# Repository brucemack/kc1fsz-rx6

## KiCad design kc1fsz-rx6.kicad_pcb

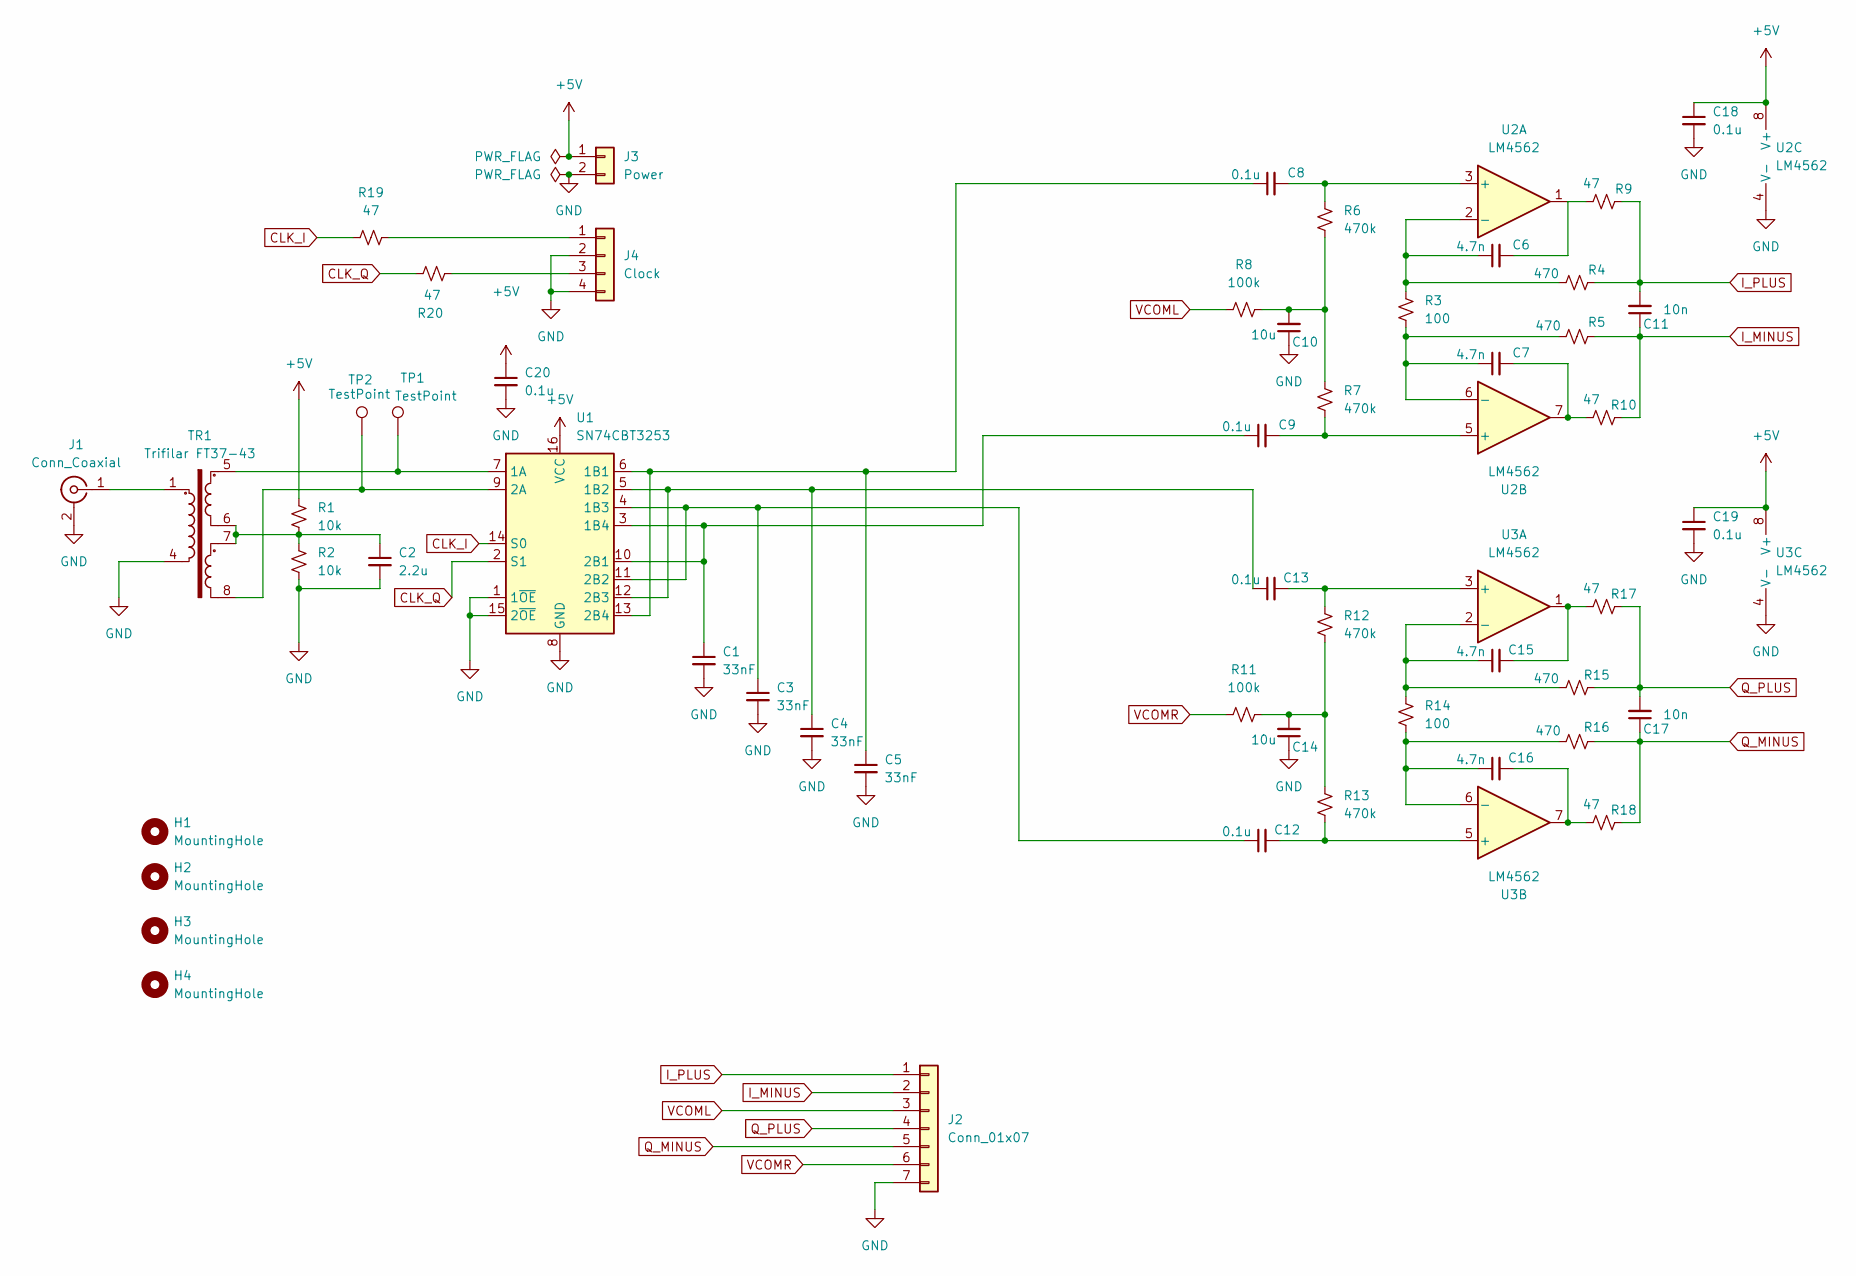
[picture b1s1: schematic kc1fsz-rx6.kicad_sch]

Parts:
C1, C3, C4, C5: 33nF; C_0805_2012Metric_Pad1.18x1.45mm_HandSolder
C2: 2.2u; C_0805_2012Metric_Pad1.18x1.45mm_HandSolder
C6, C7, C15, C16: 4.7n; C_0805_2012Metric_Pad1.18x1.45mm_HandSolder
C8, C9, C12, C13, C18, C19, C20: 0.1u; C_0805_2012Metric_Pad1.18x1.45mm_HandSolder
C10, C14: 10u; C_0805_2012Metric_Pad1.18x1.45mm_HandSolder
C11, C17: 10n; C_0805_2012Metric_Pad1.18x1.45mm_HandSolder
H1, H2, H3, H4: MountingHole; MountingHole_3.5mm
J1: Conn_Coaxial; SMA_Amphenol_901-144_Vertical
J2: Conn_01x07; PinHeader_1x07_P2.54mm_Vertical
J3: Power; PinHeader_1x02_P2.54mm_Vertical
J4: Clock; PinHeader_1x04_P2.54mm_Vertical
R1, R2: 10k; R_0805_2012Metric_Pad1.20x1.40mm_HandSolder
R3, R14: 100; R_0805_2012Metric_Pad1.20x1.40mm_HandSolder
R4, R5, R15, R16: 470; R_0805_2012Metric_Pad1.20x1.40mm_HandSolder
R6, R7, R12, R13: 470k; R_0805_2012Metric_Pad1.20x1.40mm_HandSolder
R8, R11: 100k; R_0805_2012Metric_Pad1.20x1.40mm_HandSolder
R9, R10, R17, R18, R19, R20: 47; R_0805_2012Metric_Pad1.20x1.40mm_HandSolder
TP1, TP2: TestPoint; TestPoint_Pad_1.5x1.5mm
TR1: Trifilar FT37-43; FT37-43 Trifilar
U1: SN74CBT3253; SOIC-16_3.9x9.9mm_P1.27mm
U2, U3: LM4562; SOIC-8_3.9x4.9mm_P1.27mm

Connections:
+5V: C18.1, C19.1, C20.1, J3.1, R1.1, U1.16 (VCC), U2.8 (V+), U3.8 (V+)
CLK_I: R19.1, U1.14 (S0)
CLK_Q: R20.1, U1.2 (S1)
GND: C1.2, C2.2, C3.2, C4.2, C5.2, C10.1, C14.1, C18.2, C19.2, C20.2, J1.2 (Ext), J2.7, J3.2, J4.2, J4.4, R2.2, TR1.4, U1.1 (1~OE), U1.8 (GND), U1.15 (2~OE), U2.4 (V-), U3.4 (V-)
I_MINUS: C11.1, J2.2, R5.2, R10.2
I_PLUS: C11.2, J2.1, R4.2, R9.2
unnamed: C2.1, R1.2, R2.1, TR1.6, TR1.7
unnamed: C6.2, R9.1, U2.1
unnamed: C7.2, R10.1, U2.7
unnamed: C10.2, R6.2, R7.1, R8.2
unnamed: C14.2, R11.2, R12.2, R13.1
unnamed: C15.2, R17.1, U3.1
unnamed: C16.2, R18.1, U3.7
unnamed: J1.1 (In), TR1.1
unnamed: J4.1, R19.2
unnamed: J4.3, R20.2
unnamed: TP1.1, TR1.5, U1.7 (1A)
unnamed: C5.1, C8.1, U1.6 (1B1), U1.13 (2B4)
unnamed: C4.1, C13.1, U1.5 (1B2), U1.12 (2B3)
unnamed: C3.1, C12.1, U1.4 (1B3), U1.11 (2B2)
unnamed: C1.1, C9.1, U1.3 (1B4), U1.10 (2B1)
unnamed: TP2.1, TR1.8, U1.9 (2A)
unnamed: C8.2, R6.1, U2.3 (+)
unnamed: C6.1, R3.1, R4.1, U2.2 (-)
unnamed: C9.2, R7.2, U2.5 (+)
unnamed: C7.1, R3.2, R5.1, U2.6 (-)
unnamed: C13.2, R12.1, U3.3 (+)
unnamed: C15.1, R14.1, R15.1, U3.2 (-)
unnamed: C12.2, R13.2, U3.5 (+)
unnamed: C16.1, R14.2, R16.1, U3.6 (-)
Q_MINUS: C17.1, J2.5, R16.2, R18.2
Q_PLUS: C17.2, J2.4, R15.2, R17.2
VCOML: J2.3, R8.1
VCOMR: J2.6, R11.1

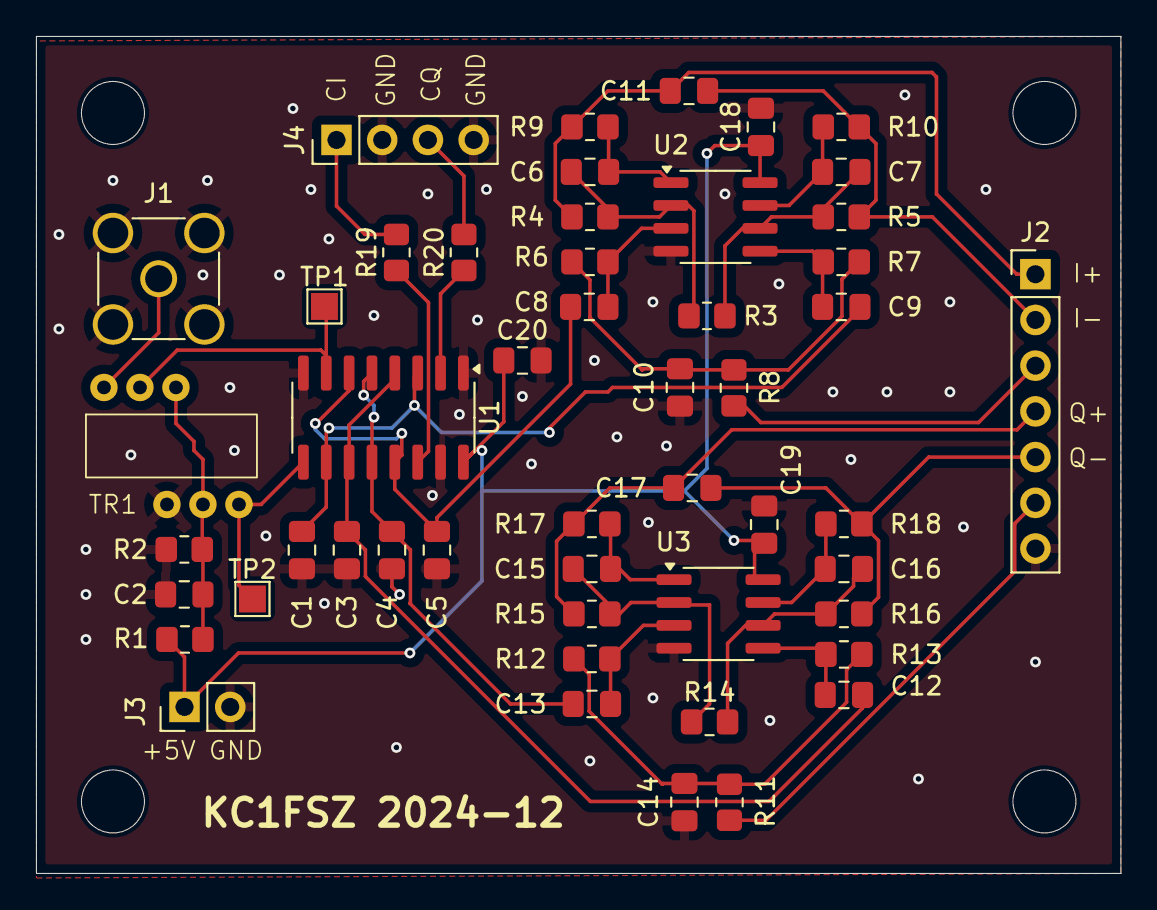
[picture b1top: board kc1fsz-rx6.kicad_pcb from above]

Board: 2 copper layers, 60.2 x 46.5 mm, 54 parts (0 on the bottom side), 34 nets.

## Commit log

2024-11-30 Working
2024-12-02 Initial PCB layout
2024-12-02 Layout complete
2024-12-02 Other tweaks after board was submitted
